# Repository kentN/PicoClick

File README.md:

# PicoClick
raspberry pi pico berakout PCB for prototyping MICROE Click boards

---
Features

- Raspberry pi pico Header

- 10pin x2 Click boards formfacter pinsockets

- additional 12pin x1 pinsocket can mount tiny I2C Display directly

- SO8W patturn for SPI ROM on SPI1 bus (See PicoClick_sch.pdf) 

- KiCad 9.0 project

1st batch config
- Rasoberry pi pico2
- SPI ROM: SST26VF064B
https://ww1.microchip.com/downloads/en/DeviceDoc/20005119G.pdf

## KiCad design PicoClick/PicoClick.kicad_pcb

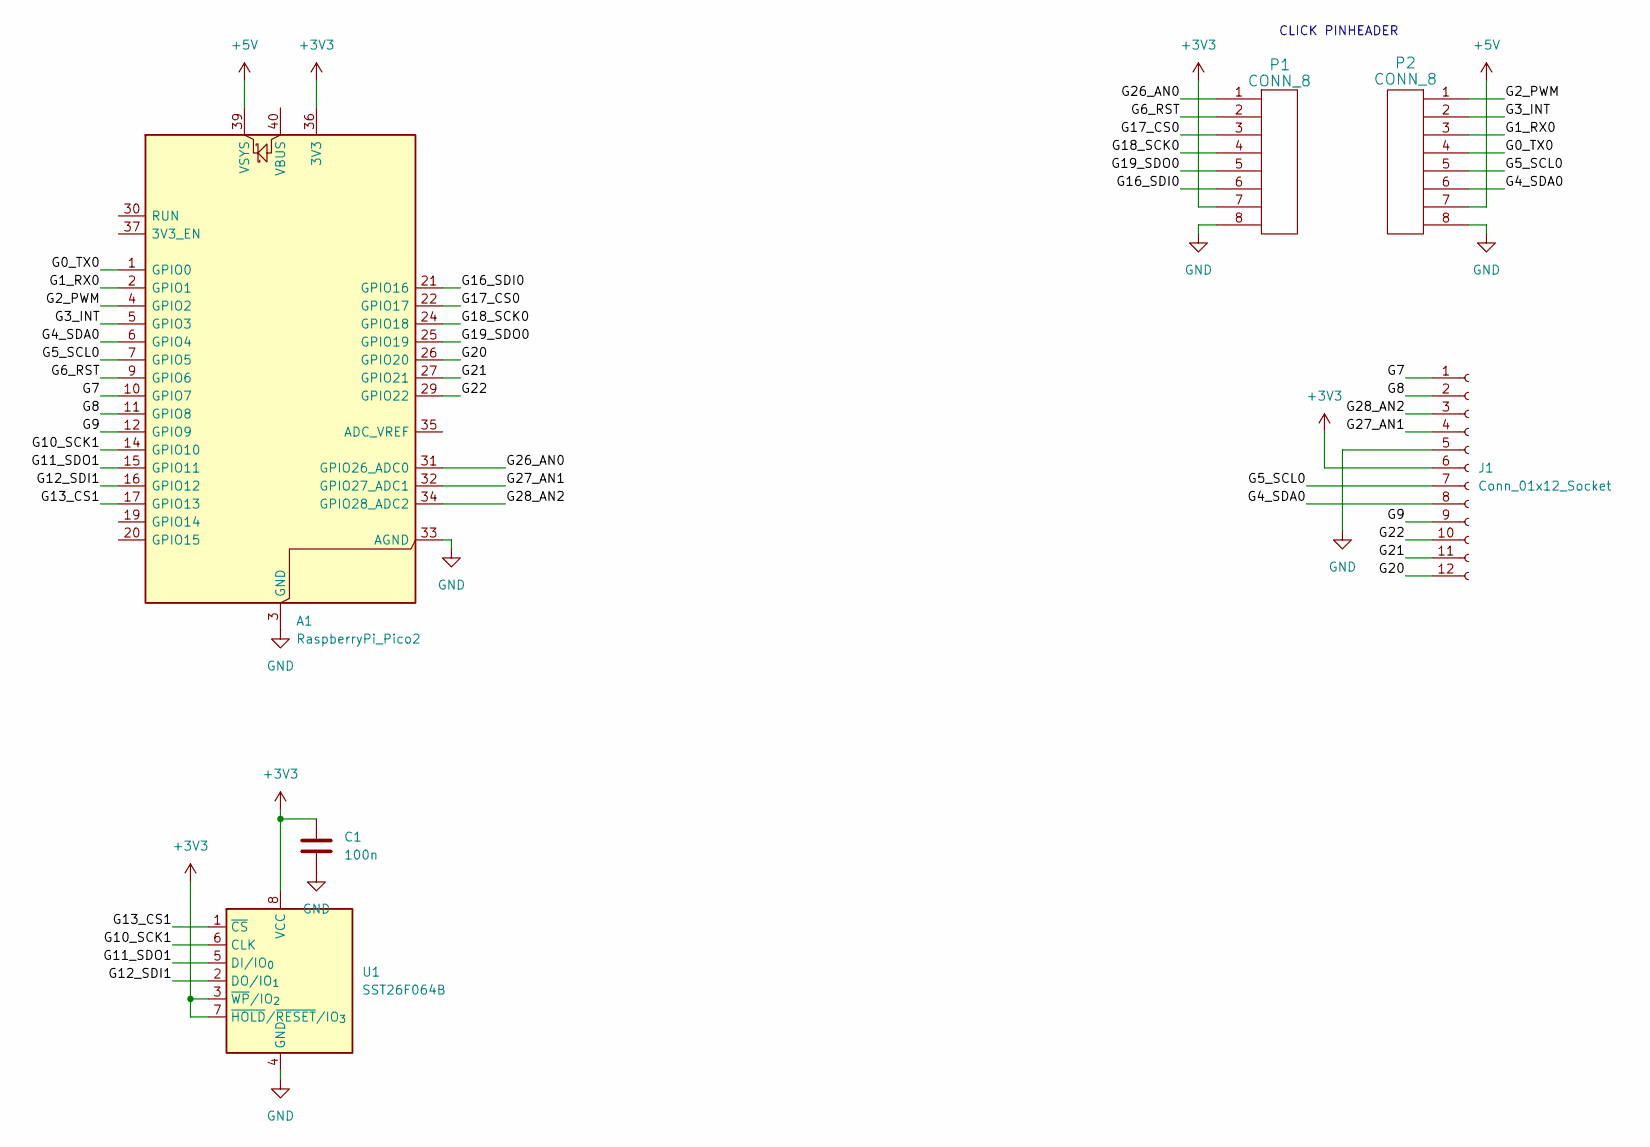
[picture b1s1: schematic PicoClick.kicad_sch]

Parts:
A1: RaspberryPi_Pico2; RaspberryPi_Pico_Common_Unspecified
C1: 100n; C_0402_1005Metric
J1: Conn_01x12_Socket; PinHeader_1x12_P2.54mm_Vertical
P1, P2: CONN_8; PinHeader_1x08_P2.54mm_Vertical
U1: SST26F064B; SOIC-8_5.3x5.3mm_P1.27mm

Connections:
+3V3: A1.36 (3V3), C1.1, J1.6, P1.7, U1.3 (~WP/IO_{2}), U1.7 (~HOLD/~RESET/IO_{3}), U1.8 (VCC)
+5V: A1.39 (VSYS), P2.7
/G0_TX0: A1.1 (GPIO0), P2.4
/G1_RX0: A1.2 (GPIO1), P2.3
/G2_PWM: A1.4 (GPIO2), P2.1
/G3_INT: A1.5 (GPIO3), P2.2
/G4_SDA0: A1.6 (GPIO4), J1.8, P2.6
/G5_SCL0: A1.7 (GPIO5), J1.7, P2.5
/G6_RST: A1.9 (GPIO6), P1.2
/G7: A1.10 (GPIO7), J1.1
/G8: A1.11 (GPIO8), J1.2
/G9: A1.12 (GPIO9), J1.9
/G10_SCK1: A1.14 (GPIO10), U1.6 (CLK)
/G11_SDO1: A1.15 (GPIO11), U1.5 (DI/IO_{0})
/G12_SDI1: A1.16 (GPIO12), U1.2 (DO/IO_{1})
/G13_CS1: A1.17 (GPIO13), U1.1 (~CS)
/G16_SDI0: A1.21 (GPIO16), P1.6
/G17_CS0: A1.22 (GPIO17), P1.3
/G18_SCK0: A1.24 (GPIO18), P1.4
/G19_SDO0: A1.25 (GPIO19), P1.5
/G20: A1.26 (GPIO20), J1.12
/G21: A1.27 (GPIO21), J1.11
/G22: A1.29 (GPIO22), J1.10
/G26_AN0: A1.31 (GPIO26_ADC0), P1.1
/G27_AN1: A1.32 (GPIO27_ADC1), J1.4
/G28_AN2: A1.34 (GPIO28_ADC2), J1.3
GND: A1.3 (GND), A1.8 (GND), A1.13 (GND), A1.18 (GND), A1.23 (GND), A1.28 (GND), A1.33 (AGND), A1.38 (GND), C1.2, J1.5, P1.8, P2.8, U1.4 (GND)

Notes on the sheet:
CLICK PINHEADER

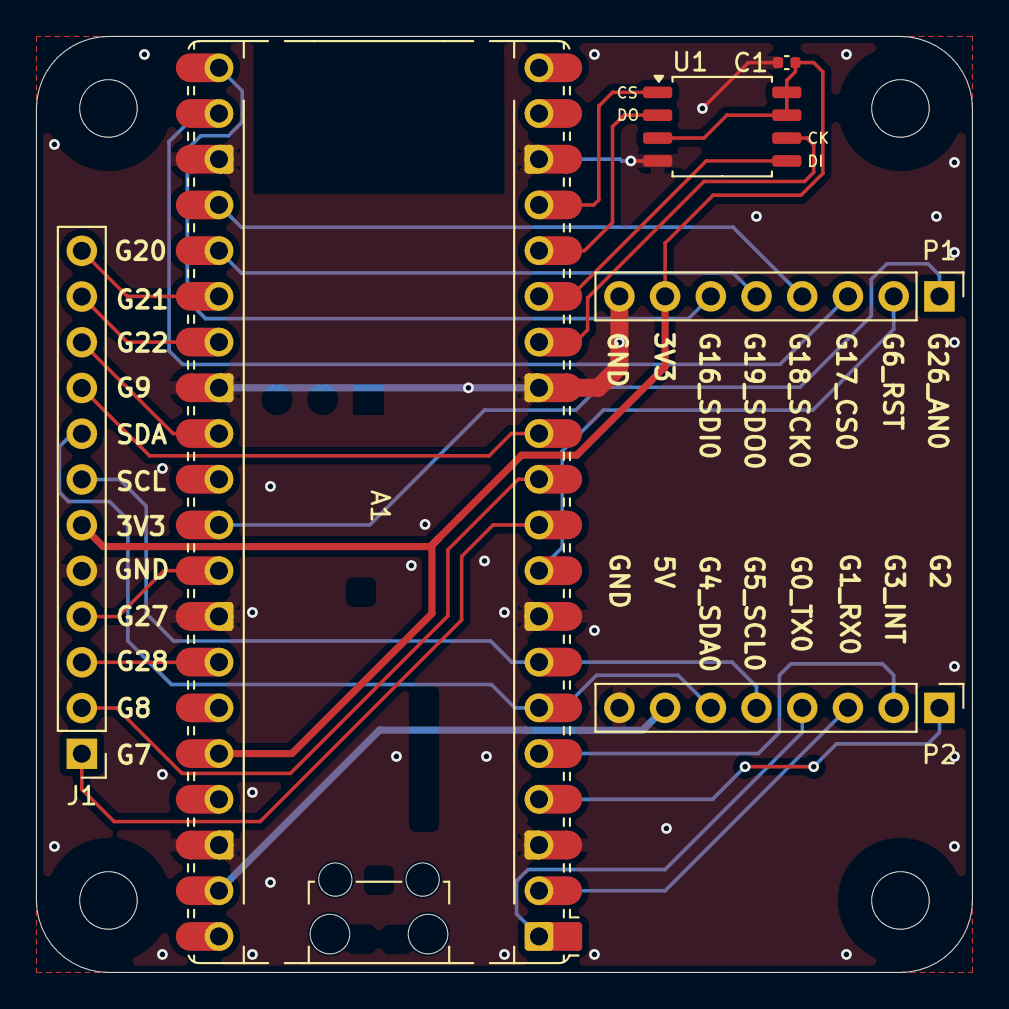
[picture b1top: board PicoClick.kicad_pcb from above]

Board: 2 copper layers, 52.0 x 52.0 mm, 6 parts (0 on the bottom side), 27 nets.

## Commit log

2025-10-19 Create .gitignore
    import from https://raw.githubusercontent.com/github/gitignore/refs/heads/main/KiCad.gitignore
2025-10-19 fix SPI labels
2025-10-19 add board image
2025-10-19 add 3Dmodel & 3DP case
2026-03-28 update kicad version (10)
